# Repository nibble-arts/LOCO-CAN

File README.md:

# LOCO-CAN

**This Loco-CAN repository is no longer supported, it [moved to a new space](https://loco-can.github.io).**

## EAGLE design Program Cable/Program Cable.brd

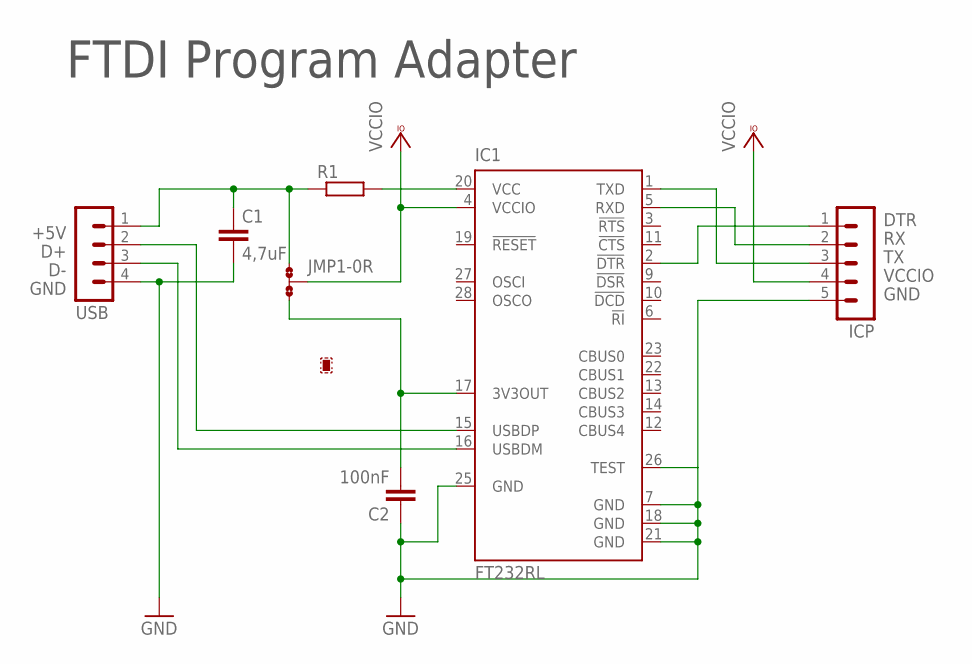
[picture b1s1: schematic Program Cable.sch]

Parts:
C1: 4,7uF; C1206
C2: 100nF; C0402
IC1: FT232RL; SSOP28
ICP: MA05-1
JMP1: 0R-JUMPA; A0R-JMP
R1: R-EU_R0805; R0805
USB: MA04-1

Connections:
3V3: C2.2, IC1.17 (3V3OUT), JMP1.3
+5V: C1.1, JMP1.1, R1.1, USB.1
D+: IC1.15 (USBDP), USB.2
D-: IC1.16 (USBDM), USB.3
DTR: IC1.2 (!DTR), ICP.1
GND: C1.2, C2.1, IC1.7 (GND), IC1.18 (GND), IC1.21 (GND), IC1.25 (GND), IC1.26 (TEST), ICP.5, USB.4
unnamed: IC1.20 (VCC), R1.2
RX: IC1.5 (RXD), ICP.2
TX: IC1.1 (TXD), ICP.3
VCCIO: IC1.4 (VCCIO), ICP.4, JMP1.2

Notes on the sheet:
FTDI Program Adapter

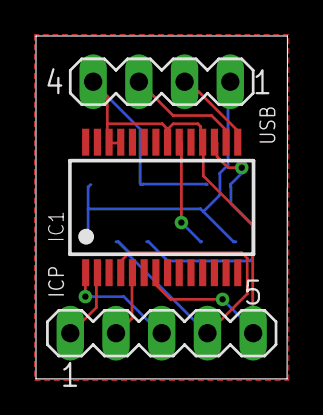
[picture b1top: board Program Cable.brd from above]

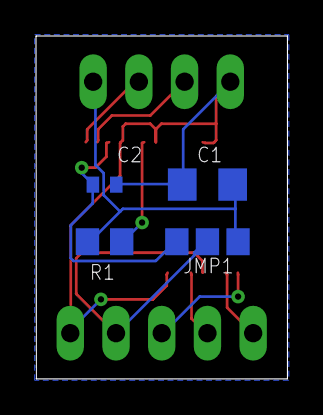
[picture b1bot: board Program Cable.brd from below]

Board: 2 copper layers, 14.0 x 19.1 mm, 7 parts (4 on the bottom side), 10 nets.

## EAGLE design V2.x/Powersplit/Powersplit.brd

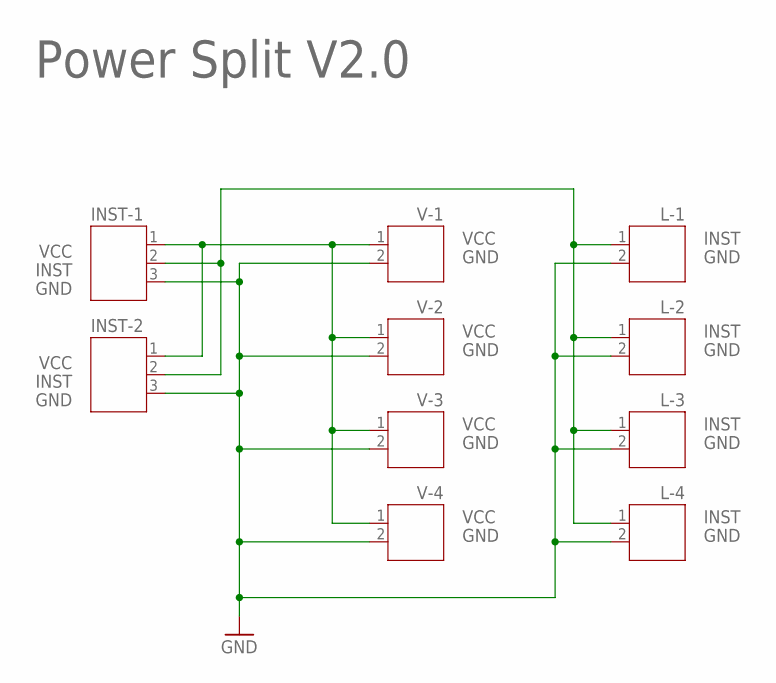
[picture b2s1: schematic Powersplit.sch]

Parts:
INST-1, INST-2: JST-PH3
L-1, L-2, L-3, L-4: JST-PH2
V-1, V-2, V-3, V-4: JST-PH2

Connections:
GND: INST-1.3, INST-2.3, L-1.2, L-2.2, L-3.2, L-4.2, V-1.2, V-2.2, V-3.2, V-4.2
INST: INST-1.2, INST-2.2, L-1.1, L-2.1, L-3.1, L-4.1
VCC: INST-1.1, INST-2.1, V-1.1, V-2.1, V-3.1, V-4.1

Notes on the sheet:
Power Split V2.0

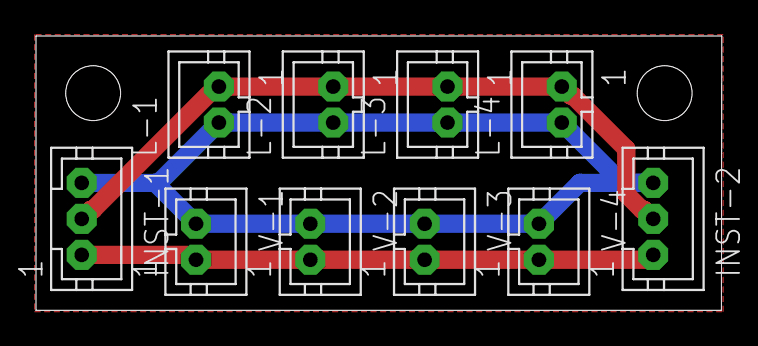
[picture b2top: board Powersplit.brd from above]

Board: 2 copper layers, 38.1 x 15.2 mm, 10 parts (0 on the bottom side), 3 nets.

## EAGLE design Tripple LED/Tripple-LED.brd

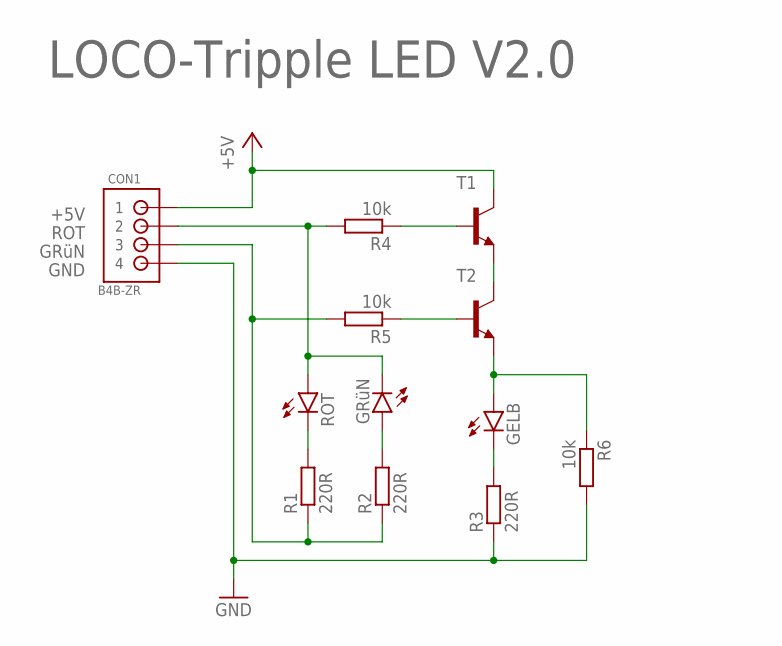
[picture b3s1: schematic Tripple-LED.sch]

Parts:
CON1: B4B-ZR
GELB: LED5MM
GRüN: LED5MM
R1, R2, R3: 220R; R0402
R4, R5, R6: 10k; R0402
ROT: LED5MM
T1, T2: -NPN-SOT23-EBC; SOT23-EBC

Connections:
+5V: CON1.1, T1.C
GND: CON1.4, R3.1, R6.2
GRüN: CON1.3, R1.1, R2.1, R5.2
unnamed: GRüN.A, R2.2
unnamed: R1.2, ROT.K (C)
unnamed: GELB.K (C), R3.2
unnamed: R4.1, T1.B
unnamed: R5.1, T2.B
unnamed: T1.E, T2.C
unnamed: GELB.A, R6.1, T2.E
ROT: CON1.2, GRüN.K (C), R4.2, ROT.A

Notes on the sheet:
LOCO-Tripple LED V2.0

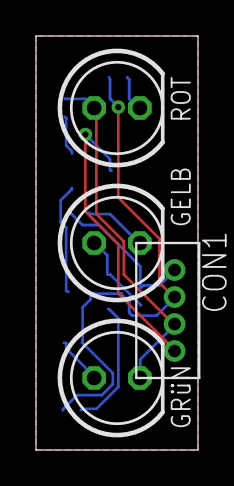
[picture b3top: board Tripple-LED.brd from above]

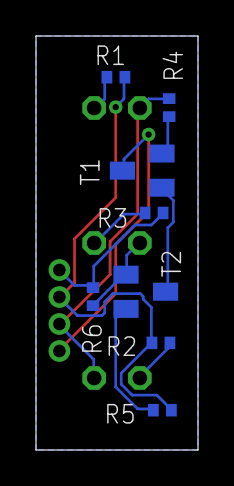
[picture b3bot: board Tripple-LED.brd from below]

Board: 2 copper layers, 9.0 x 23.0 mm, 12 parts (8 on the bottom side), 11 nets.

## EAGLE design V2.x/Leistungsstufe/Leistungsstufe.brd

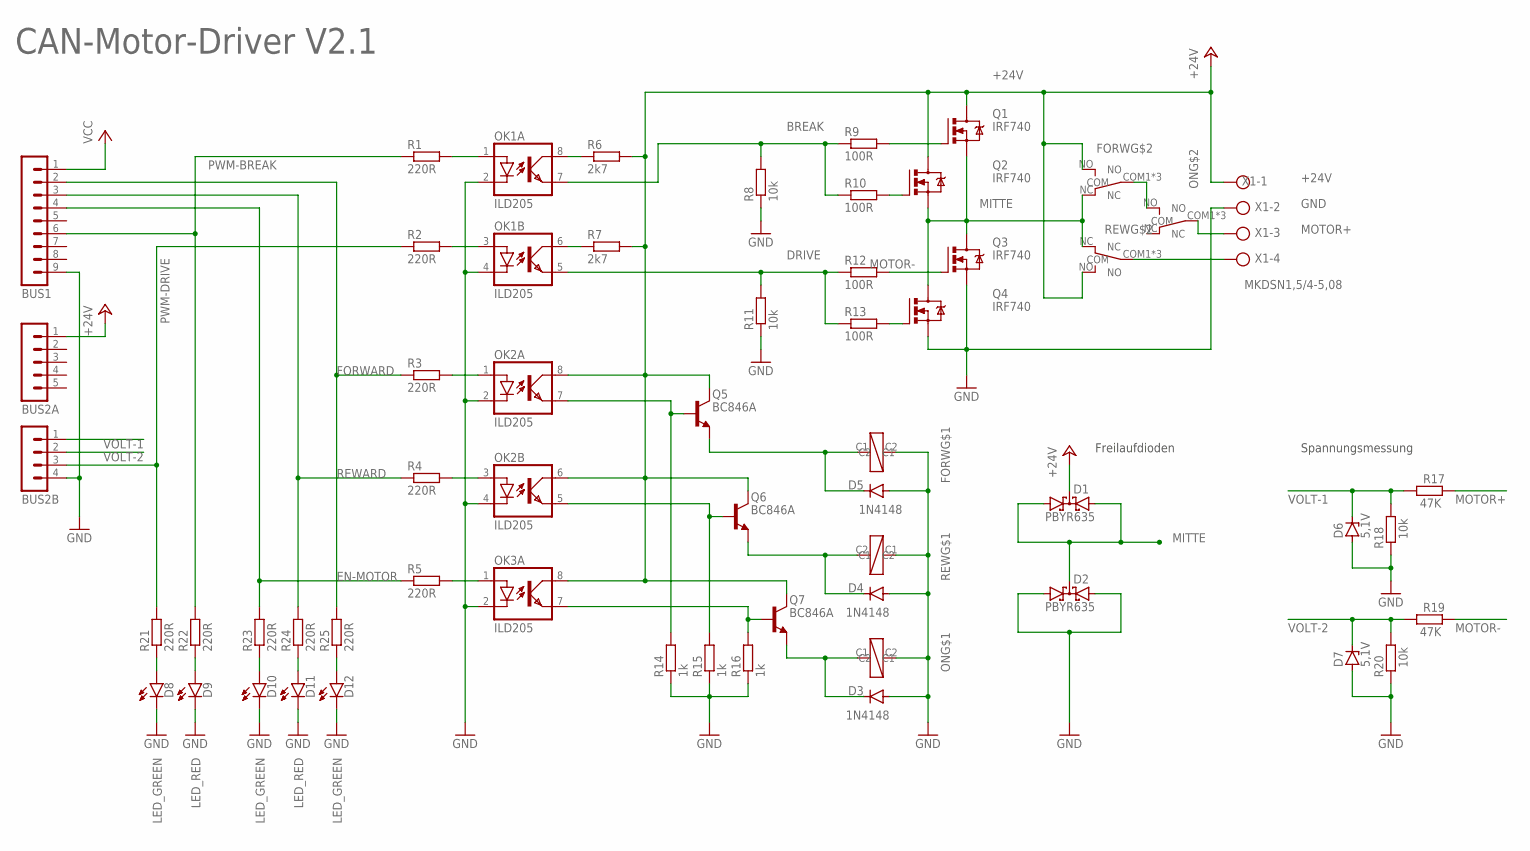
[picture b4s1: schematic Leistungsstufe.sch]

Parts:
BUS1: MA09-1
BUS2A: MA05-1
BUS2B: MA04-1
D1, D2: PBYR635; SOT82S
D3, D4, D5: 1N4148; SOD323-R
D6, D7: 5,1V; SOD80C
D8, D10, D12: LED_GREEN; LEDC1608X39N_G
D9, D11: LED_RED; LEDC1608X39N_R
FORW: FRA2C-2
OK1, OK2, OK3: ILD205; SOIC08
ON: FRA2C-2
Q1, Q2, Q3, Q4: IRF740; TO220BV
Q5, Q6, Q7: BC846A; SOT95P237X112-3N
R1, R2, R3, R4, R5, R21, R22, R23, R24, R25: 220R; R0805
R6, R7: 2k7; R0805
R8, R11: 10k; R0805
R9, R10, R12, R13: 100R; R0805
R14, R15, R16: 1k; R0805
R17, R19: 47K; MINI_MELF-0102W
R18, R20: 10k; MINI_MELF-0102W
REW: FRA2C-2
X1: MKDSN1,5/4-5,08

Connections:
+24V: BUS2A.1, D1.C, FORW.NO, OK2.6 (COL), OK2.8 (COL), OK3.8 (COL), Q1.D, Q2.D, Q5.3 (C), Q6.3 (C), Q7.3 (C), R6.2, R7.2, REW.NO, X1.1
BREAK: OK1.7 (EMIT), R8.2, R9.1, R10.1
DRIVE: OK1.5 (EMIT), R11.2, R12.1, R13.1
EN-MOTOR: BUS1.4, R5.1, R23.2
FORWARD: BUS1.2, R3.1, R25.2
GND: BUS1.9, BUS2B.4, D2.A1, D2.A2, D3.A, D4.A, D5.A, D6.A, D7.A, D8.1 (C), D9.1 (C), D10.1 (C), D11.1 (C), D12.1 (C), FORW.C2, OK1.2 (C), OK1.4 (C), OK2.2 (C), OK2.4 (C), OK3.2 (C), ON.C2, Q3.S, Q4.S, R8.1, R11.1, R14.1, R15.1, R16.1, R18.1, R20.1, REW.C1, X1.2
M+SWITCH: FORW.COM1 (COM), FORW.COM2 (COM), FORW.COM3 (COM), ON.NO
MITTE: D1.A1, D1.A2, D2.C, FORW.NC, Q1.S, Q2.S, Q3.D, Q4.D, REW.NC
MOTOR+: ON.COM1 (COM), ON.COM2 (COM), ON.COM3 (COM), R17.2, X1.3
MOTOR-: R19.2, REW.COM1 (COM), REW.COM2 (COM), REW.COM3 (COM), X1.4
unnamed: Q2.G, R10.2
unnamed: Q3.G, R12.2
unnamed: Q4.G, R13.2
unnamed: OK2.7 (EMIT), Q5.1 (B), R14.2
unnamed: Q1.G, R9.2
unnamed: OK1.3 (A), R2.2
unnamed: D4.C, Q6.2 (E), REW.C2
unnamed: D8.2 (A), R21.1
unnamed: D5.C, FORW.C1, Q5.2 (E)
unnamed: OK2.5 (EMIT), Q6.1 (B), R15.2
unnamed: D3.C, ON.C1, Q7.2 (E)
unnamed: OK1.8 (COL), R6.1
unnamed: OK1.6 (COL), R7.1
unnamed: OK1.1 (A), R1.2
unnamed: OK2.1 (A), R3.2
unnamed: OK2.3 (A), R4.2
unnamed: OK3.1 (A), R5.2
unnamed: OK3.7 (EMIT), Q7.1 (B), R16.2
unnamed: D10.2 (A), R23.1
unnamed: D9.2 (A), R22.1
unnamed: D11.2 (A), R24.1
unnamed: D12.2 (A), R25.1
PWM-BREAK: BUS1.6, R1.1, R22.2
PWM-DRIVE: BUS2B.3, R2.1, R21.2
REWARD: BUS1.3, R4.1, R24.2
VCC: BUS1.1
VOLT-1: BUS2B.1, D6.C, R17.1, R18.2
VOLT-2: BUS2B.2, D7.C, R19.1, R20.2

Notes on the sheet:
Freilaufdioden
Spannungsmessung
CAN-Motor-Driver V2.1

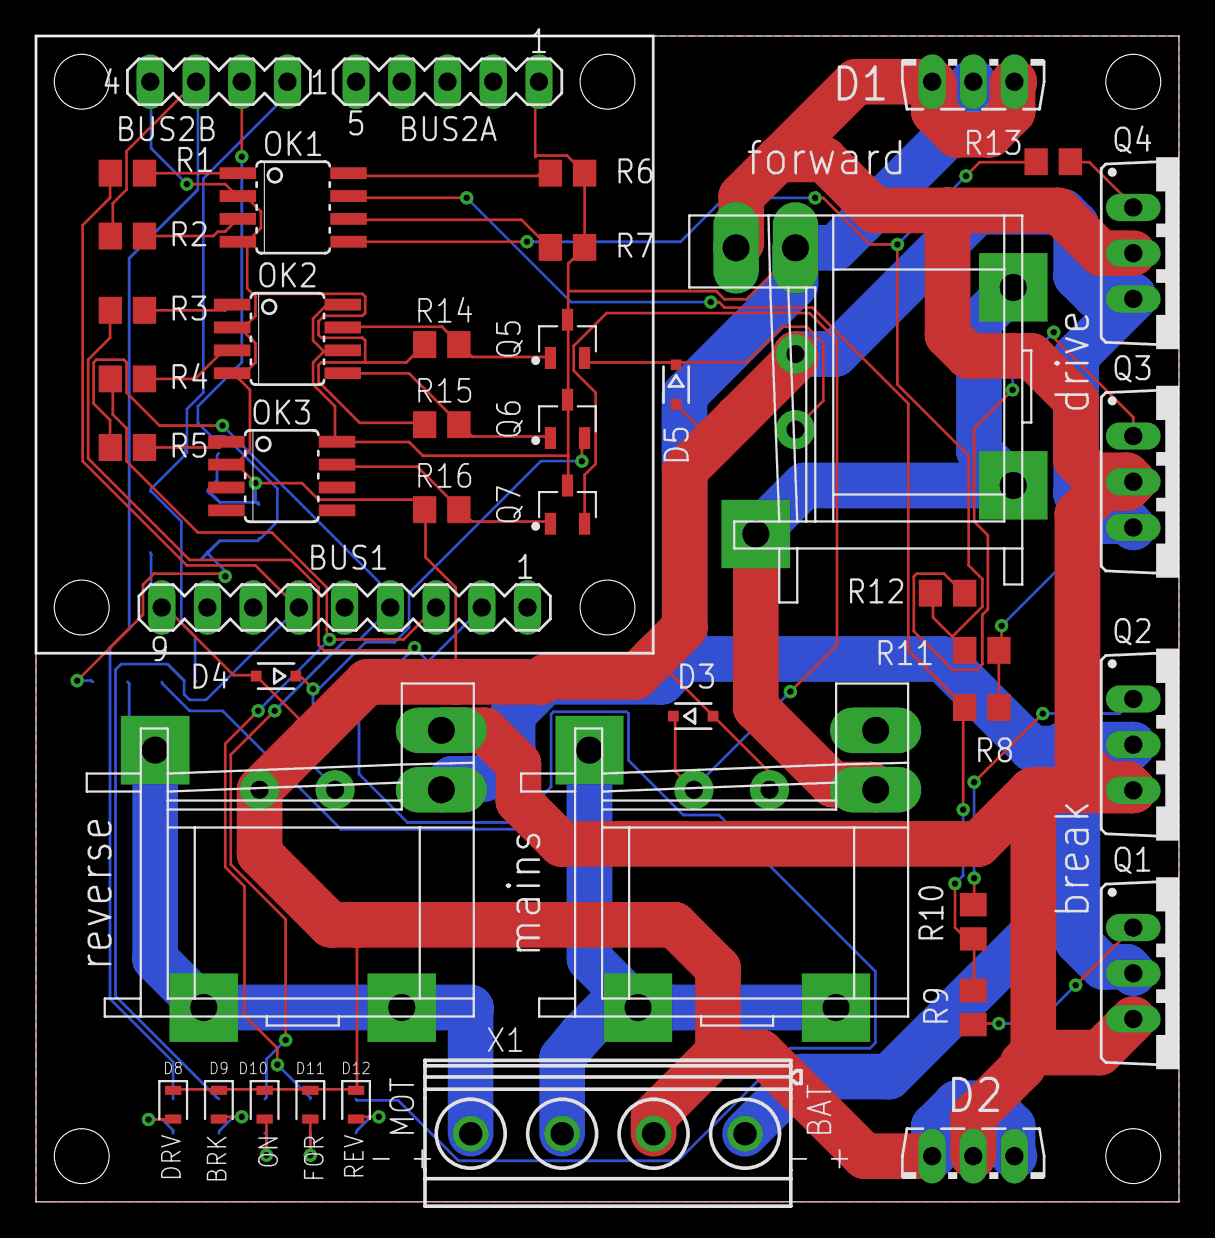
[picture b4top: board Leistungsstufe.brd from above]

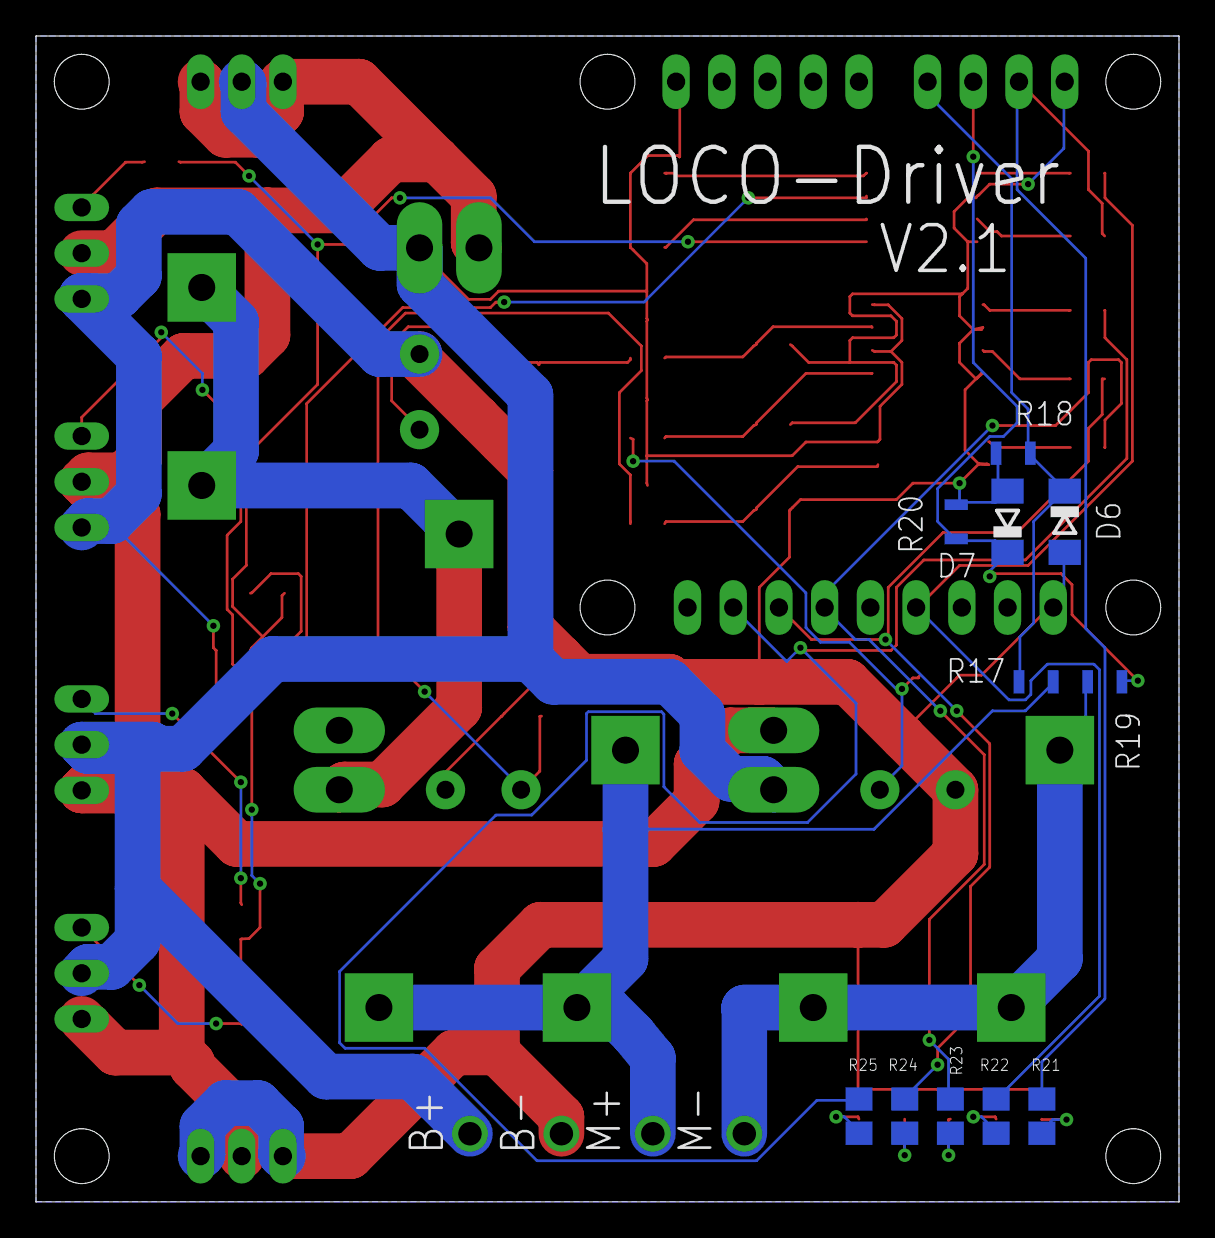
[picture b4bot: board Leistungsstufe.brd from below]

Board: 2 copper layers, 63.5 x 64.8 mm, 54 parts (11 on the bottom side), 37 nets.

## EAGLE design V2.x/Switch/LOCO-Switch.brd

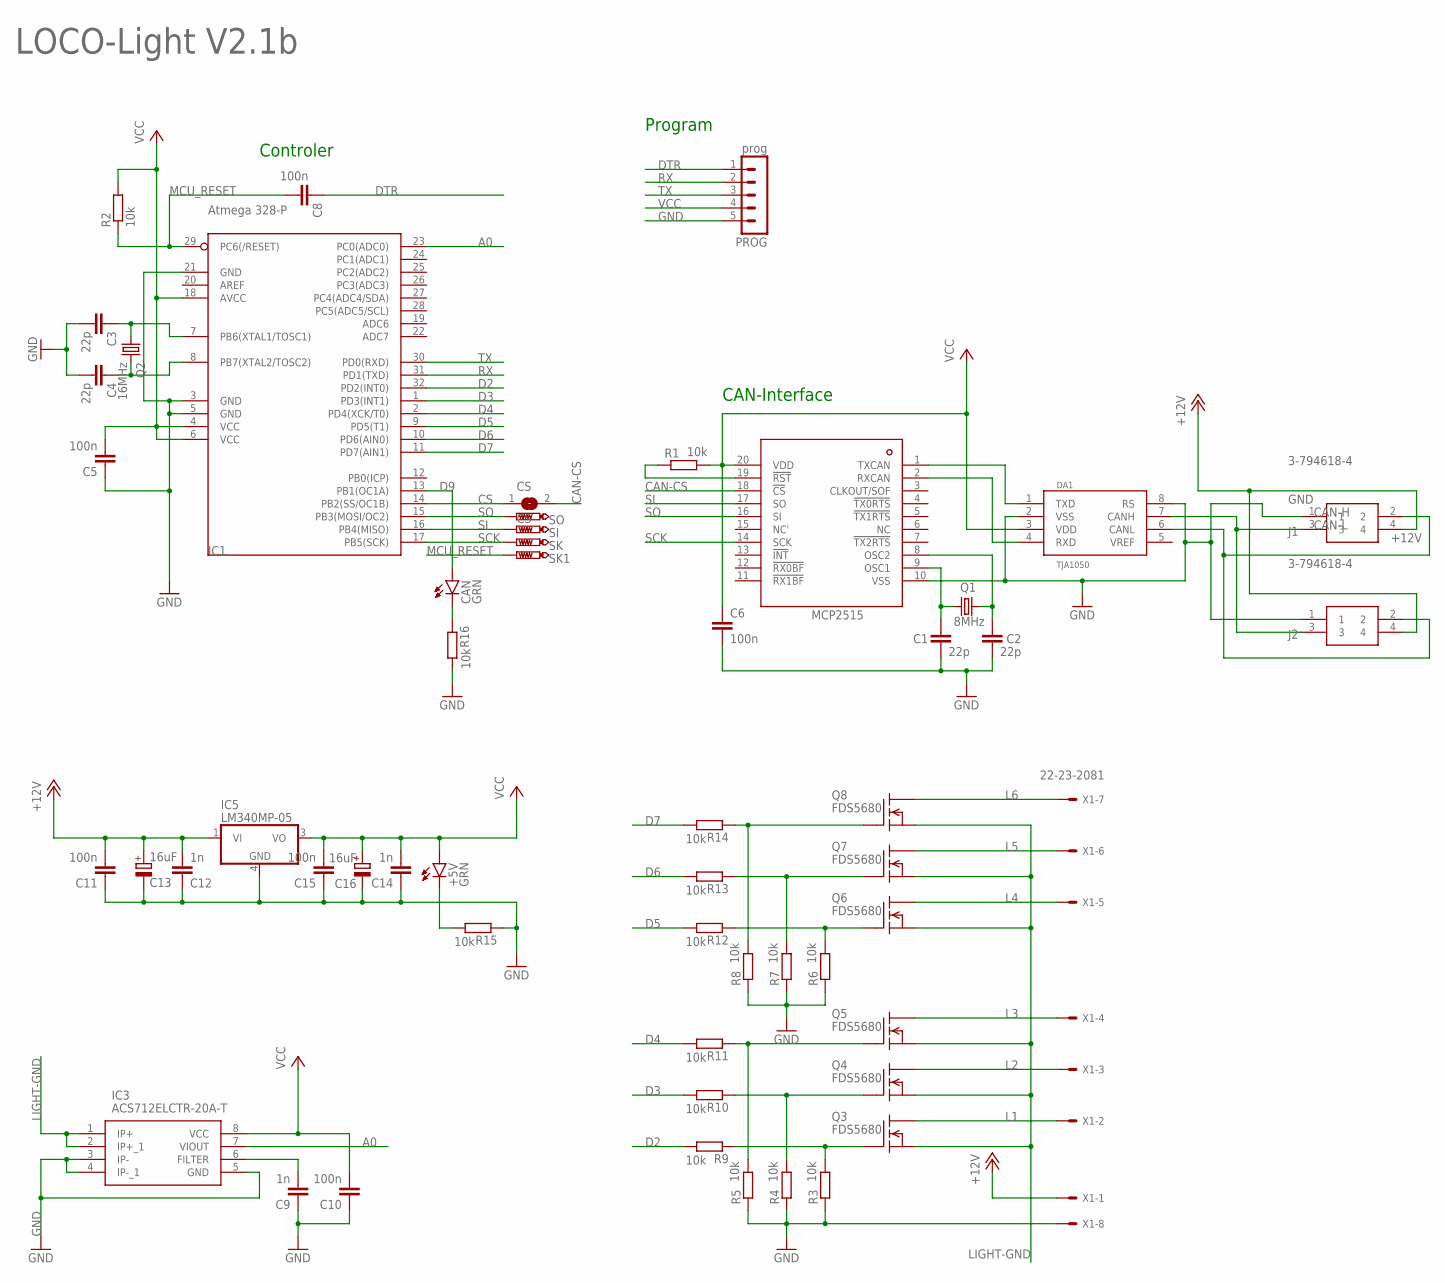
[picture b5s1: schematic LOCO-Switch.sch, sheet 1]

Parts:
+5V: GRN; CHIP-LED0603
C1, C2, C3, C4: 22p; C0402K
C5, C6, C8, C10, C11, C15: 100n; C0402K
C9, C12, C14: 1n; C0402K
C13, C16: 16uF; A/3216-18W
CAN: GRN; CHIP-LED0603
CS: CS; SJ
DA1: TJA1050; SO08
IC1: Atmega 328-P; TQFP32-08
IC2: MCP2515; TSSOP20
IC3: ACS712ELCTR-20A-T; SOIC127P600X175-8N
IC5: LM340MP-05; SOT223
J1, J2: 3-794618-4; SHDRRA4W102P300_2X2_686X892X73
PROG: prog; MA05-1
Q1: 8MHz; HC49/S
Q2: 16MHz; HC49/S
Q3, Q4, Q5, Q6, Q7, Q8: FDS5680; SO-8
R1, R2, R3, R4, R5, R6, R7, R8, R9, R10, R11, R12, R13, R14, R15, R16: 10k; R0603
SI: PTR1B1,27; B1,27
SK, SK1: PTR1B1,27; B1,27
SO: PTR1B1,27; B1,27
X1: 22-23-2081

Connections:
+12V: C11.2, C12.2, C13.+, IC5.1 (VI), J1.4, J2.4, X1.1
A0: IC1.23 (PC0(ADC0)), IC3.7 (VIOUT)
CAN-CS: CS.2, IC2.18 (!CS)
CAN-H: DA1.7 (CANH), J1.3, J2.3
CAN-L: DA1.6 (CANL), J1.2, J2.2
CAN-OCC1: C1.1, IC2.9 (OSC1), Q1.1
CAN-OCC2: C2.1, IC2.8 (OSC2), Q1.2
CS: CS.1, IC1.14 (PB2(SS/OC1B))
D2: IC1.32 (PD2(INT0)), R9.2
D3: IC1.1 (PD3(INT1)), R10.2
D4: IC1.2 (PD4(XCK/T0)), R11.2
D5: IC1.9 (PD5(T1)), R12.2
D6: IC1.10 (PD6(AIN0)), R13.2
D7: IC1.11 (PD7(AIN1)), R14.2
D9: CAN.A, IC1.13 (PB1(OC1A))
DTR: C8.1, PROG.1
GND: C1.2, C2.2, C3.2, C4.2, C5.1, C6.2, C9.1, C10.1, C11.1, C12.1, C13.-, C14.1, C15.1, C16.-, DA1.2 (VSS), DA1.8 (RS), IC1.3 (GND), IC1.5 (GND), IC1.21 (GND), IC2.10 (VSS), IC3.3 (IP-), IC3.4 (IP-_1), IC3.5 (GND), IC5.4 (GND), J1.1, J2.1, PROG.5, R3.1, R4.1, R5.1, R6.1, R7.1, R8.1, R15.1, R16.2, X1.8
L1: Q3.5 (D), Q3.6 (D), Q3.7 (D), Q3.8 (D), X1.2
L2: Q4.5 (D), Q4.6 (D), Q4.7 (D), Q4.8 (D), X1.3
L3: Q5.5 (D), Q5.6 (D), Q5.7 (D), Q5.8 (D), X1.4
L4: Q6.5 (D), Q6.6 (D), Q6.7 (D), Q6.8 (D), X1.5
L5: Q7.5 (D), Q7.6 (D), Q7.7 (D), Q7.8 (D), X1.6
L6: Q8.5 (D), Q8.6 (D), Q8.7 (D), Q8.8 (D), X1.7
LIGHT-GND: IC3.1 (IP+), IC3.2 (IP+_1), Q3.1 (S), Q3.2 (S), Q3.3 (S), Q4.1 (S), Q4.2 (S), Q4.3 (S), Q5.1 (S), Q5.2 (S), Q5.3 (S), Q6.1 (S), Q6.2 (S), Q6.3 (S), Q7.1 (S), Q7.2 (S), Q7.3 (S), Q8.1 (S), Q8.2 (S), Q8.3 (S)
MCU_RESET: C8.2, IC1.29 (PC6(/RESET)), R2.1, SK1.TP
unnamed: C9.2, IC3.6 (FILTER)
unnamed: Q3.4 (G), R3.2, R9.1
unnamed: Q4.4 (G), R4.2, R10.1
unnamed: Q5.4 (G), R5.2, R11.1
unnamed: Q6.4 (G), R6.2, R12.1
unnamed: IC2.19 (!RST), R1.1
unnamed: Q7.4 (G), R7.2, R13.1
unnamed: Q8.4 (G), R8.2, R14.1
unnamed: CAN.C, R16.1
unnamed: C3.1, IC1.7 (PB6(XTAL1/TOSC1)), Q2.1
unnamed: C4.1, IC1.8 (PB7(XTAL2/TOSC2)), Q2.2
unnamed: +5V.C, R15.2
RX: IC1.31 (PD1(TXD)), PROG.2
RXCAN: DA1.4 (RXD), IC2.2 (RXCAN)
SCK: IC1.17 (PB5(SCK)), IC2.14 (SCK), SK.TP
SI: IC1.16 (PB4(MISO)), IC2.17 (SO), SI.TP
SO: IC1.15 (PB3(MOSI/OC2)), IC2.16 (SI), SO.TP
TX: IC1.30 (PD0(RXD)), PROG.3
TXCAN: DA1.1 (TXD), IC2.1 (TXCAN)
VCC: +5V.A, C5.2, C6.1, C10.2, C14.2, C15.2, C16.+, DA1.3 (VDD), IC1.4 (VCC), IC1.6 (VCC), IC1.18 (AVCC), IC2.20 (VDD), IC3.8 (VCC), IC5.3 (VO), PROG.4, R1.2, R2.2

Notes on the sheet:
Program
CAN-Interface
Controler
LOCO-Light V2.1b

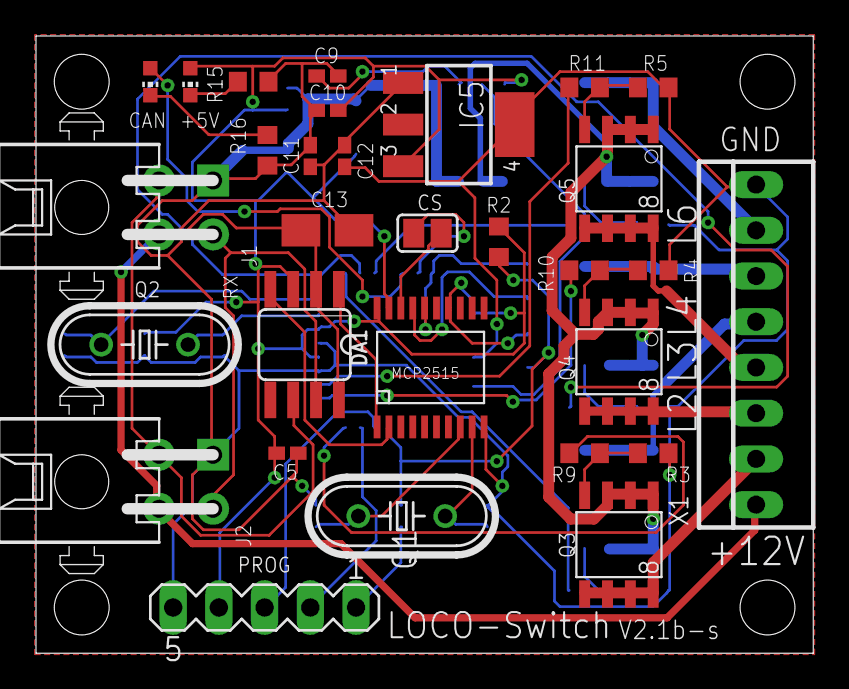
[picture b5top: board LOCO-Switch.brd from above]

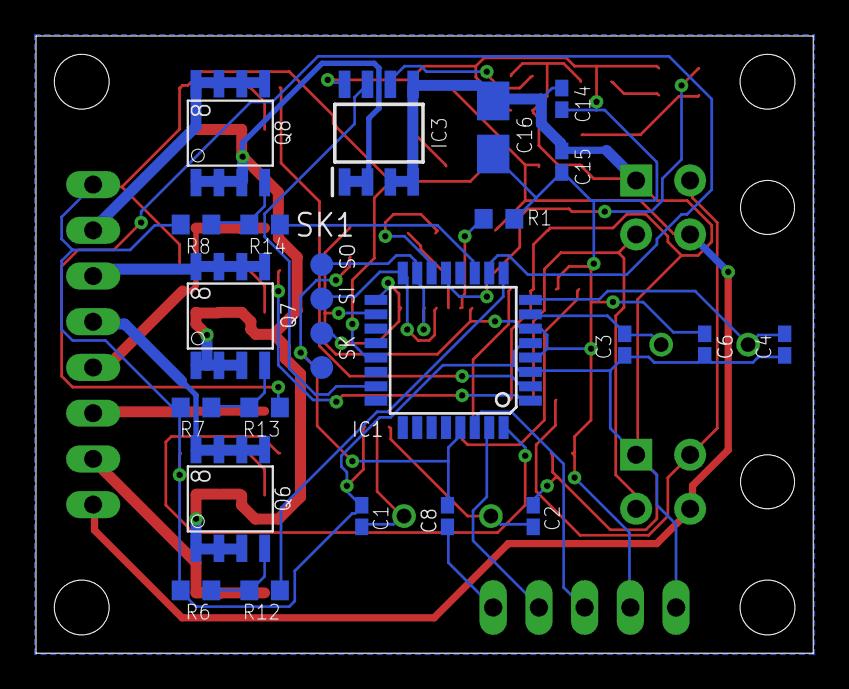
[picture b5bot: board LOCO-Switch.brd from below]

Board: 2 copper layers, 43.2 x 34.3 mm, 55 parts (25 on the bottom side), 45 nets.

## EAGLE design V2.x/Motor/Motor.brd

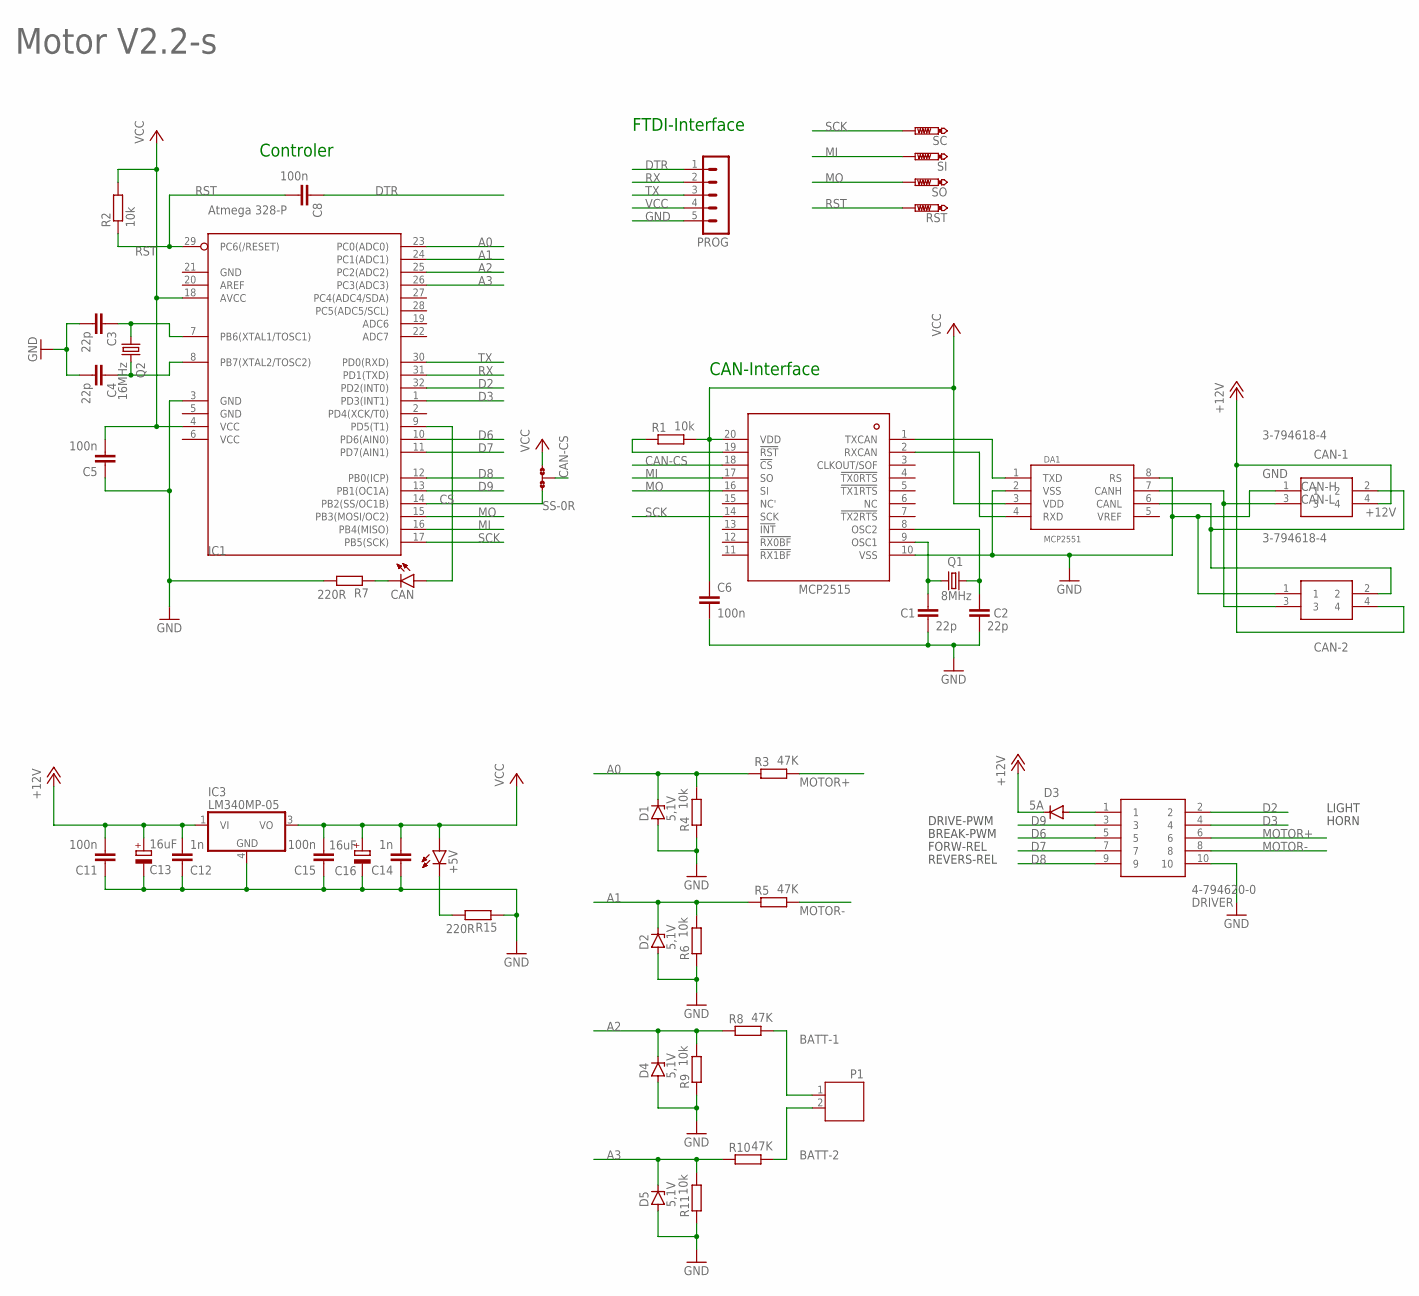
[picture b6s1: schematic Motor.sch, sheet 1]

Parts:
+5V: LEDCHIP-LED0603; CHIP-LED0603
C1, C2, C3, C4: 22p; C0402K
C5, C6, C8, C11, C15: 100n; C0402K
C12, C14: 1n; C0402K
C13, C16: 16uF; A/3216-18W
CAN: LEDCHIP-LED0603; CHIP-LED0603
CAN-1, CAN-2: 3-794618-4; SHDRRA4W102P300_2X2_686X892X73
D1, D2, D4, D5: 5,1V; SOD80C
D3: 5A; DO214AA
DA1: MCP2551; SO08
DRIVER: 4-794620-0; 47946200
IC1: Atmega 328-P; TQFP32-08
IC2: MCP2515; TSSOP20
IC3: LM340MP-05; SOT223
P1: JST-PH2
PROG: MA05-1
Q1: 8MHz; HC49/S
Q2: 16MHz; HC49/S
R1, R2: 10k; R0805
R3, R5, R8, R10: 47K; MINI_MELF-0102W
R4, R6, R9, R11: 10k; MINI_MELF-0102W
R7, R15: 220R; R0805
RST: PTR1B1,27; B1,27
SC: PTR1B1,27; B1,27
SI: PTR1B1,27; B1,27
SO: PTR1B1,27; B1,27
SS: 0R-JUMPA; A0R-JMP

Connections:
+12V: C11.2, C12.2, C13.+, CAN-1.4, CAN-2.4, D3.C, IC3.1 (VI)
A0: D1.C, IC1.23 (PC0(ADC0)), R3.1, R4.2
A1: D2.C, IC1.24 (PC1(ADC1)), R5.1, R6.2
A2: D4.C, IC1.25 (PC2(ADC2)), R8.1, R9.2
A3: D5.C, IC1.26 (PC3(ADC3)), R10.1, R11.2
BATT-1: P1.1, R8.2
BATT-2: P1.2, R10.2
CAN-CS: IC2.18 (!CS), SS.2
CAN-H: CAN-1.3, CAN-2.3, DA1.7 (CANH)
CAN-L: CAN-1.2, CAN-2.2, DA1.6 (CANL)
CAN-OCC1: C1.1, IC2.9 (OSC1), Q1.1
CAN-OCC2: C2.1, IC2.8 (OSC2), Q1.2
CS: IC1.14 (PB2(SS/OC1B)), SS.3
D2: DRIVER.2, IC1.32 (PD2(INT0))
D3: DRIVER.4, IC1.1 (PD3(INT1))
D6: DRIVER.5, IC1.10 (PD6(AIN0))
D7: DRIVER.7, IC1.11 (PD7(AIN1))
D8: DRIVER.9, IC1.12 (PB0(ICP))
D9: DRIVER.3, IC1.13 (PB1(OC1A))
DTR: C8.1, PROG.1
GND: C1.2, C2.2, C3.2, C4.2, C5.1, C6.2, C11.1, C12.1, C13.-, C14.1, C15.1, C16.-, CAN-1.1, CAN-2.1, D1.A, D2.A, D4.A, D5.A, DA1.2 (VSS), DA1.8 (RS), DRIVER.10, IC1.3 (GND), IC1.5 (GND), IC1.21 (GND), IC2.10 (VSS), IC3.4 (GND), PROG.5, R4.1, R6.1, R7.2, R9.1, R11.1, R15.1
MI: IC1.16 (PB4(MISO)), IC2.17 (SO), SI.TP
MO: IC1.15 (PB3(MOSI/OC2)), IC2.16 (SI), SO.TP
MOTOR+: DRIVER.6, R3.2
MOTOR-: DRIVER.8, R5.2
unnamed: D3.A, DRIVER.1
unnamed: CAN.C, R7.1
unnamed: CAN.A, IC1.9 (PD5(T1))
unnamed: IC2.19 (!RST), R1.1
unnamed: C3.1, IC1.7 (PB6(XTAL1/TOSC1)), Q2.1
unnamed: C4.1, IC1.8 (PB7(XTAL2/TOSC2)), Q2.2
unnamed: +5V.C, R15.2
RST: C8.2, IC1.29 (PC6(/RESET)), R2.1, RST.TP
RX: IC1.31 (PD1(TXD)), PROG.2
RXCAN: DA1.4 (RXD), IC2.2 (RXCAN)
SCK: IC1.17 (PB5(SCK)), IC2.14 (SCK), SC.TP
TX: IC1.30 (PD0(RXD)), PROG.3
TXCAN: DA1.1 (TXD), IC2.1 (TXCAN)
VCC: +5V.A, C5.2, C6.1, C14.2, C15.2, C16.+, DA1.3 (VDD), IC1.4 (VCC), IC1.6 (VCC), IC1.18 (AVCC), IC2.20 (VDD), IC3.3 (VO), PROG.4, R1.2, R2.2, SS.1

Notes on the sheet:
FTDI-Interface
CAN-Interface
Controler
DRIVE-PWM
BREAK-PWM
LIGHT
FORW-REL
REVERS-REL
HORN
Motor V2.2-s

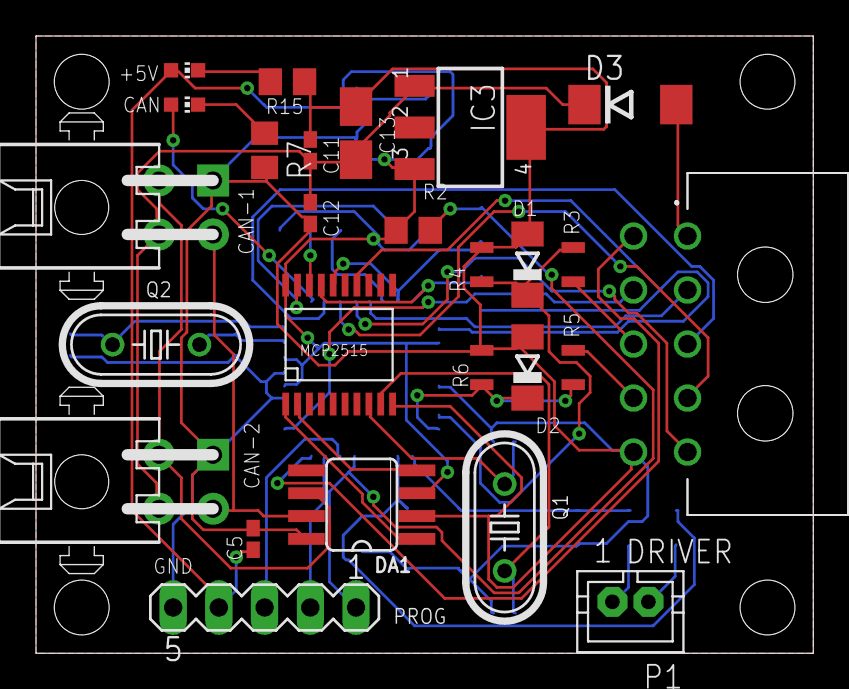
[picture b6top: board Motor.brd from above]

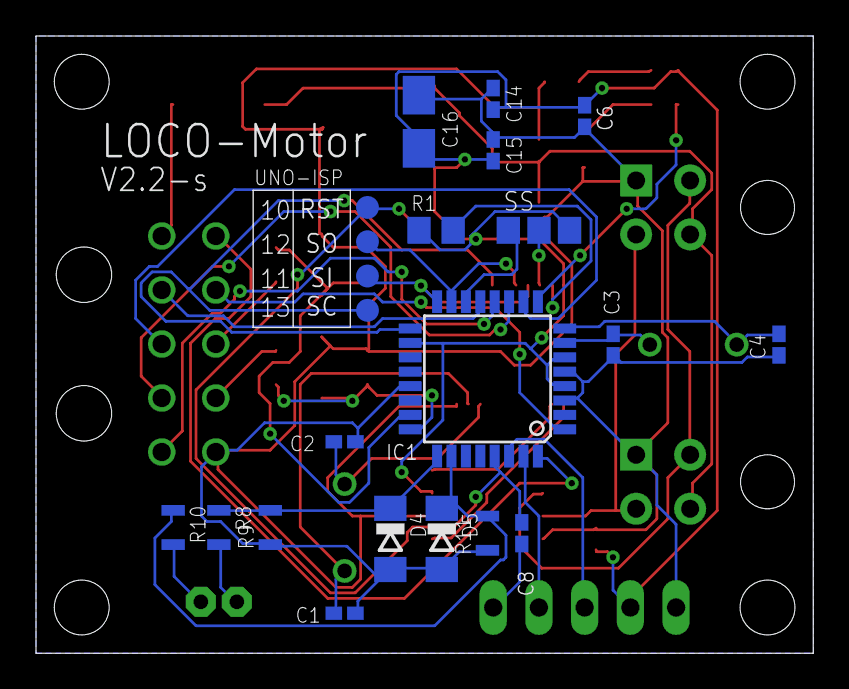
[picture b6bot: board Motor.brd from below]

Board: 2 copper layers, 43.2 x 34.3 mm, 48 parts (22 on the bottom side), 39 nets.

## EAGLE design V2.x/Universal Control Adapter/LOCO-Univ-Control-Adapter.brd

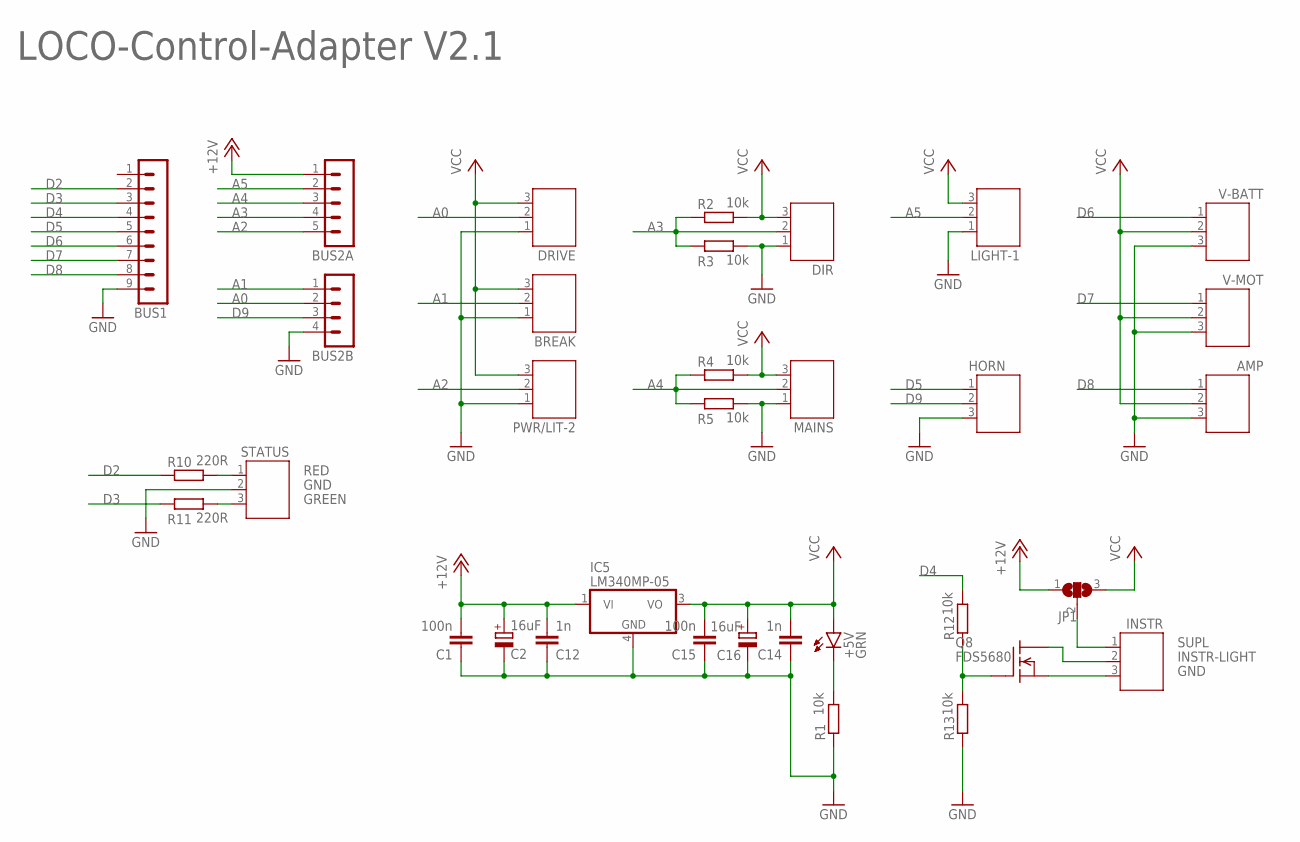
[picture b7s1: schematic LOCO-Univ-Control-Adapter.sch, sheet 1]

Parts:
+5V: GRN; CHIP-LED0603
AMP: JST-PH3
BREAK: JST-PH3
BUS1: MA09-1
BUS2A: MA05-1
BUS2B: MA04-1
C1, C15: 100n; C0402K
C2, C16: 16uF; A/3216-18W
C12, C14: 1n; C0402K
DIR: JST-PH3
DRIVE: JST-PH3
HORN: JST-PH3
IC5: LM340MP-05; SOT223
INSTR: JST-PH3
JP1: SJ2W; SJ_2
LIGHT-1: JST-PH3
MAINS: JST-PH3
PWR/LIT-2: JST-PH3
Q8: FDS5680; SO-8
R1, R12, R13: 10k; R0603
R2, R3, R4, R5: 10k; R0805
R10, R11: 220R; R0805
STATUS: JST-PH3
V-BATT: JST-PH3
V-MOT: JST-PH3

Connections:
+12V: BUS2A.1, C1.2, C2.+, C12.2, IC5.1 (VI), JP1.1
A0: BUS2B.2, DRIVE.2
A1: BREAK.2, BUS2B.1
A2: BUS2A.5, PWR/LIT-2.2
A3: BUS2A.4, DIR.2, R2.1, R3.1
A4: BUS2A.3, MAINS.2, R4.1, R5.1
A5: BUS2A.2, LIGHT-1.2
D2: BUS1.2, R10.1
D3: BUS1.3, R11.1
D4: BUS1.4, R12.2
D5: BUS1.5, HORN.1
D6: BUS1.6, V-BATT.1
D7: BUS1.7, V-MOT.1
D8: AMP.1, BUS1.8
D9: BUS2B.3, HORN.2
GND: AMP.3, BREAK.1, BUS1.9, BUS2B.4, C1.1, C2.-, C12.1, C14.1, C15.1, C16.-, DIR.1, DRIVE.1, HORN.3, IC5.4 (GND), INSTR.3, LIGHT-1.1, MAINS.1, PWR/LIT-2.1, Q8.1 (S), Q8.2 (S), Q8.3 (S), R1.1, R3.2, R5.2, R13.1, STATUS.2, V-BATT.3, V-MOT.3
GREEN: R11.2, STATUS.3
INSTR-LIGHT: INSTR.2, Q8.5 (D), Q8.6 (D), Q8.7 (D), Q8.8 (D)
unnamed: Q8.4 (G), R12.1, R13.2
unnamed: +5V.C, R1.2
RED: R10.2, STATUS.1
SUPL: INSTR.1, JP1.2
VCC: +5V.A, AMP.2, BREAK.3, C14.2, C15.2, C16.+, DIR.3, DRIVE.3, IC5.3 (VO), JP1.3, LIGHT-1.3, MAINS.3, PWR/LIT-2.3, R2.2, R4.2, V-BATT.2, V-MOT.2

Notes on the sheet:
LOCO-Control-Adapter V2.1

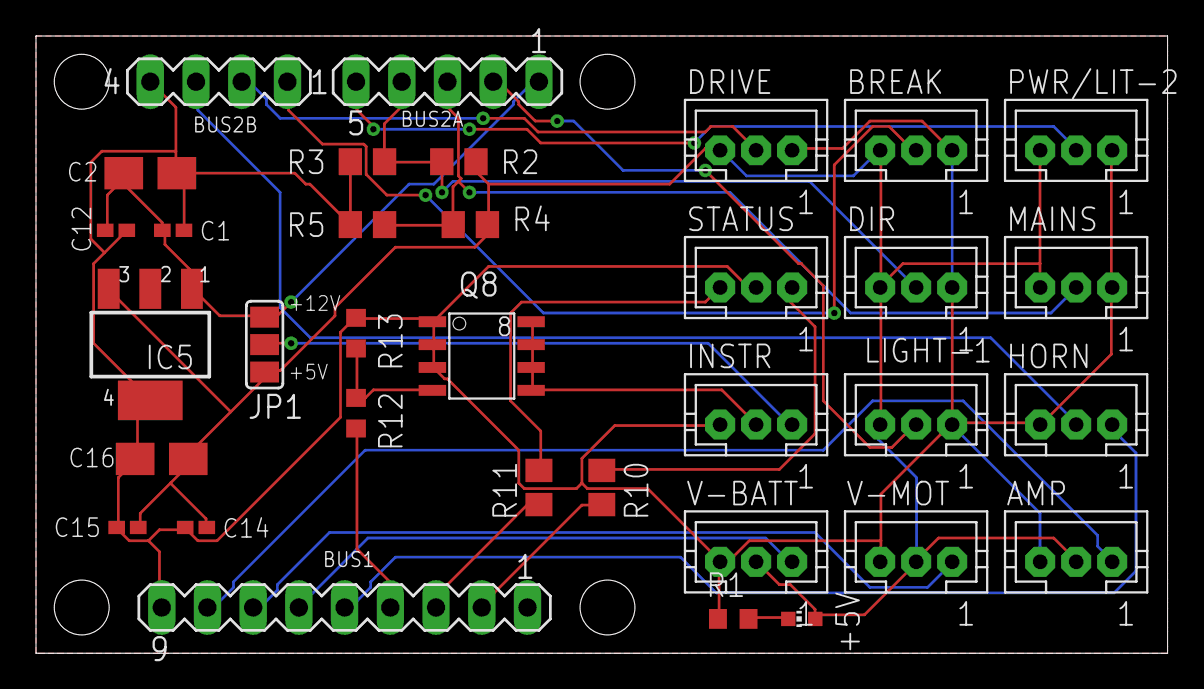
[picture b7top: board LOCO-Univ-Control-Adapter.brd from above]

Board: 2 copper layers, 62.9 x 34.3 mm, 34 parts (0 on the bottom side), 23 nets.

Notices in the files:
parts and their libraries:
crystal-geyer_V1_0: Copyright: Geyer-Electronic
COPYRIGHT: Copyright (C) 2023 Ultra Librarian. All rights reserved.
